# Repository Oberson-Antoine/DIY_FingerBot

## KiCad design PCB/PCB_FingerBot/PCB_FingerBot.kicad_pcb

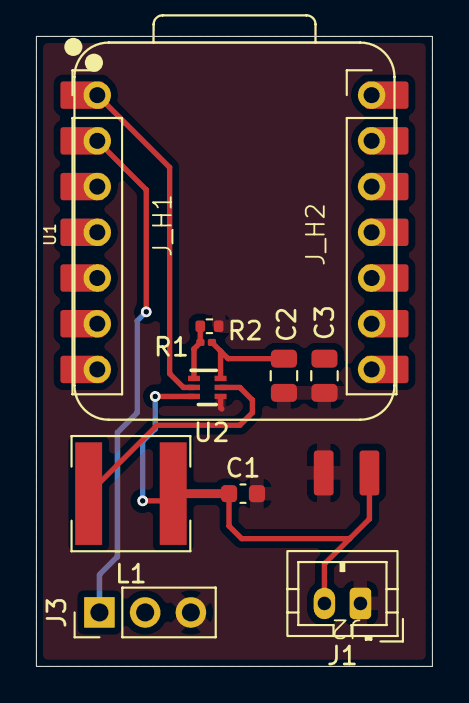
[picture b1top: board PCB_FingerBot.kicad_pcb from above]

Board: 2 copper layers, 22.0 x 35.0 mm, 13 parts (0 on the bottom side), 7 nets.

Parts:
C1: 10 μF; C_0603_1608Metric
C2, C3: 22 μF; C_0805_2012Metric
J1: Conn_01x02_Pin; JST_PH_B2B-PH-K_1x02_P2.00mm_Vertical
J2: Conn_2_pads; Pads 1x2 2.54mm Battery
J3: Conn_01x03_Pin; PinHeader_1x03_P2.54mm_Vertical
J_H1, J_H2: PinHeader_1x07_P2.54_INVISIBLE
L1: 2.7 μH; L_6.3x6.3_H3
R1: 732k; R_0201_0603Metric
R2: 100k; R_0402_1005Metric
U1: XIAO-ESP32-C6-SMD; XIAO-ESP32-C6-DIP
U2: TPS61023DRLR; DRL0006A

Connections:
5V - Servo: C2.1, C3.1, R1.2, U2.6 (VOUT)
GND: C1.2, C2.2, C3.2, J1.1, J2.2, J3.3, R2.1, U2.4 (GND)
unnamed: R1.1, R2.2, U2.1 (FB)
unnamed: L1.2, U2.5 (SW)
Servo - EN: U1.1 (D0), U2.2 (EN)
Servo - PWM: J3.1, U1.2 (D1)
VBAT: C1.1, J1.2, J2.1, L1.1, U2.3 (VIN)
